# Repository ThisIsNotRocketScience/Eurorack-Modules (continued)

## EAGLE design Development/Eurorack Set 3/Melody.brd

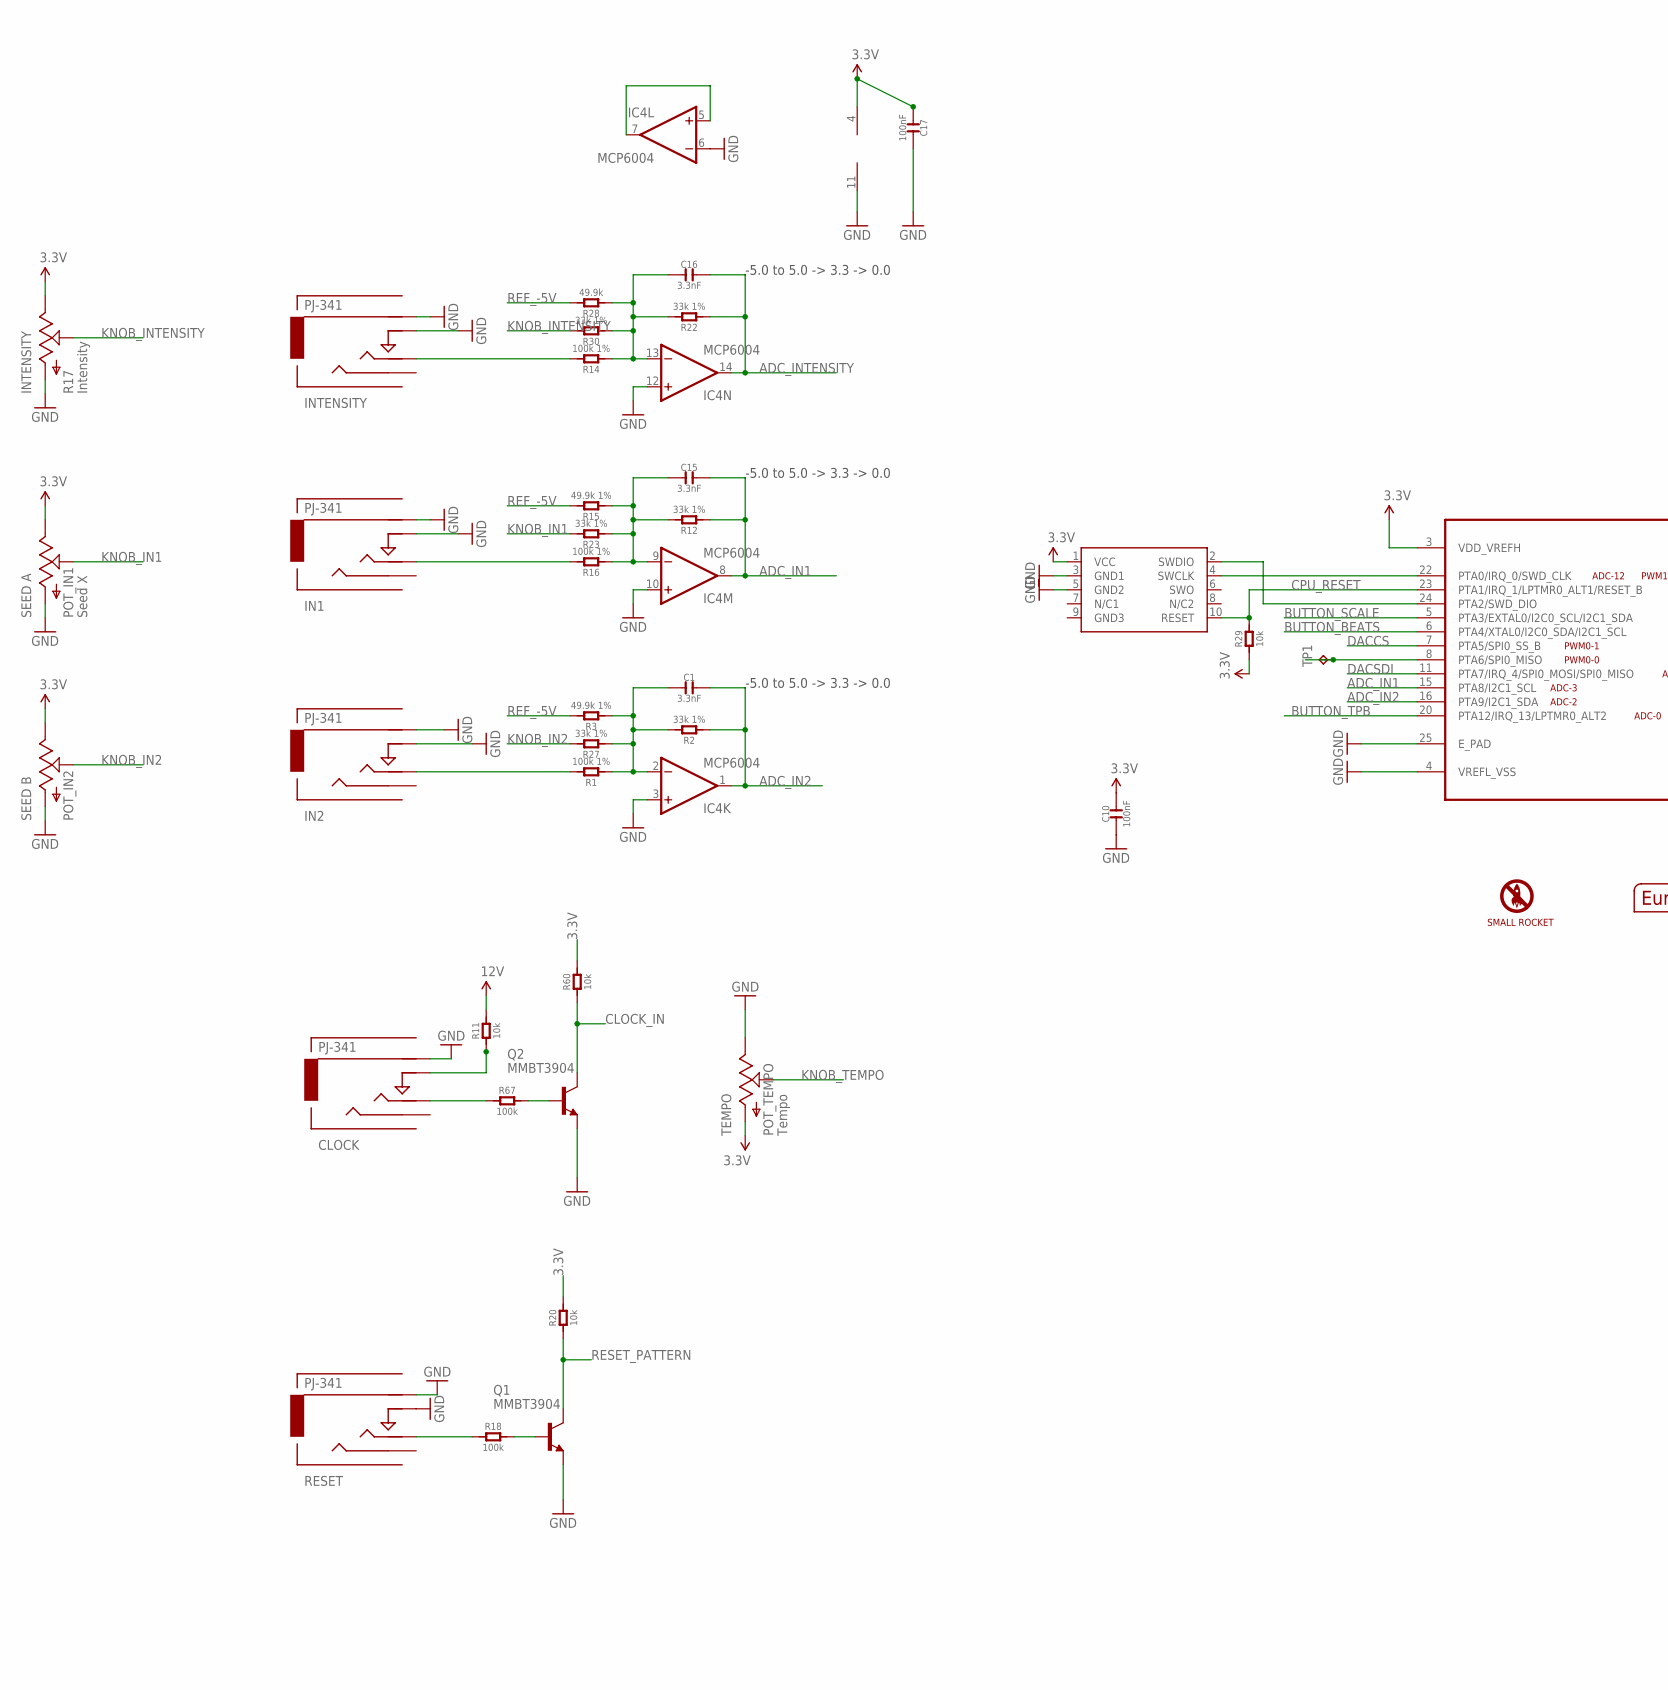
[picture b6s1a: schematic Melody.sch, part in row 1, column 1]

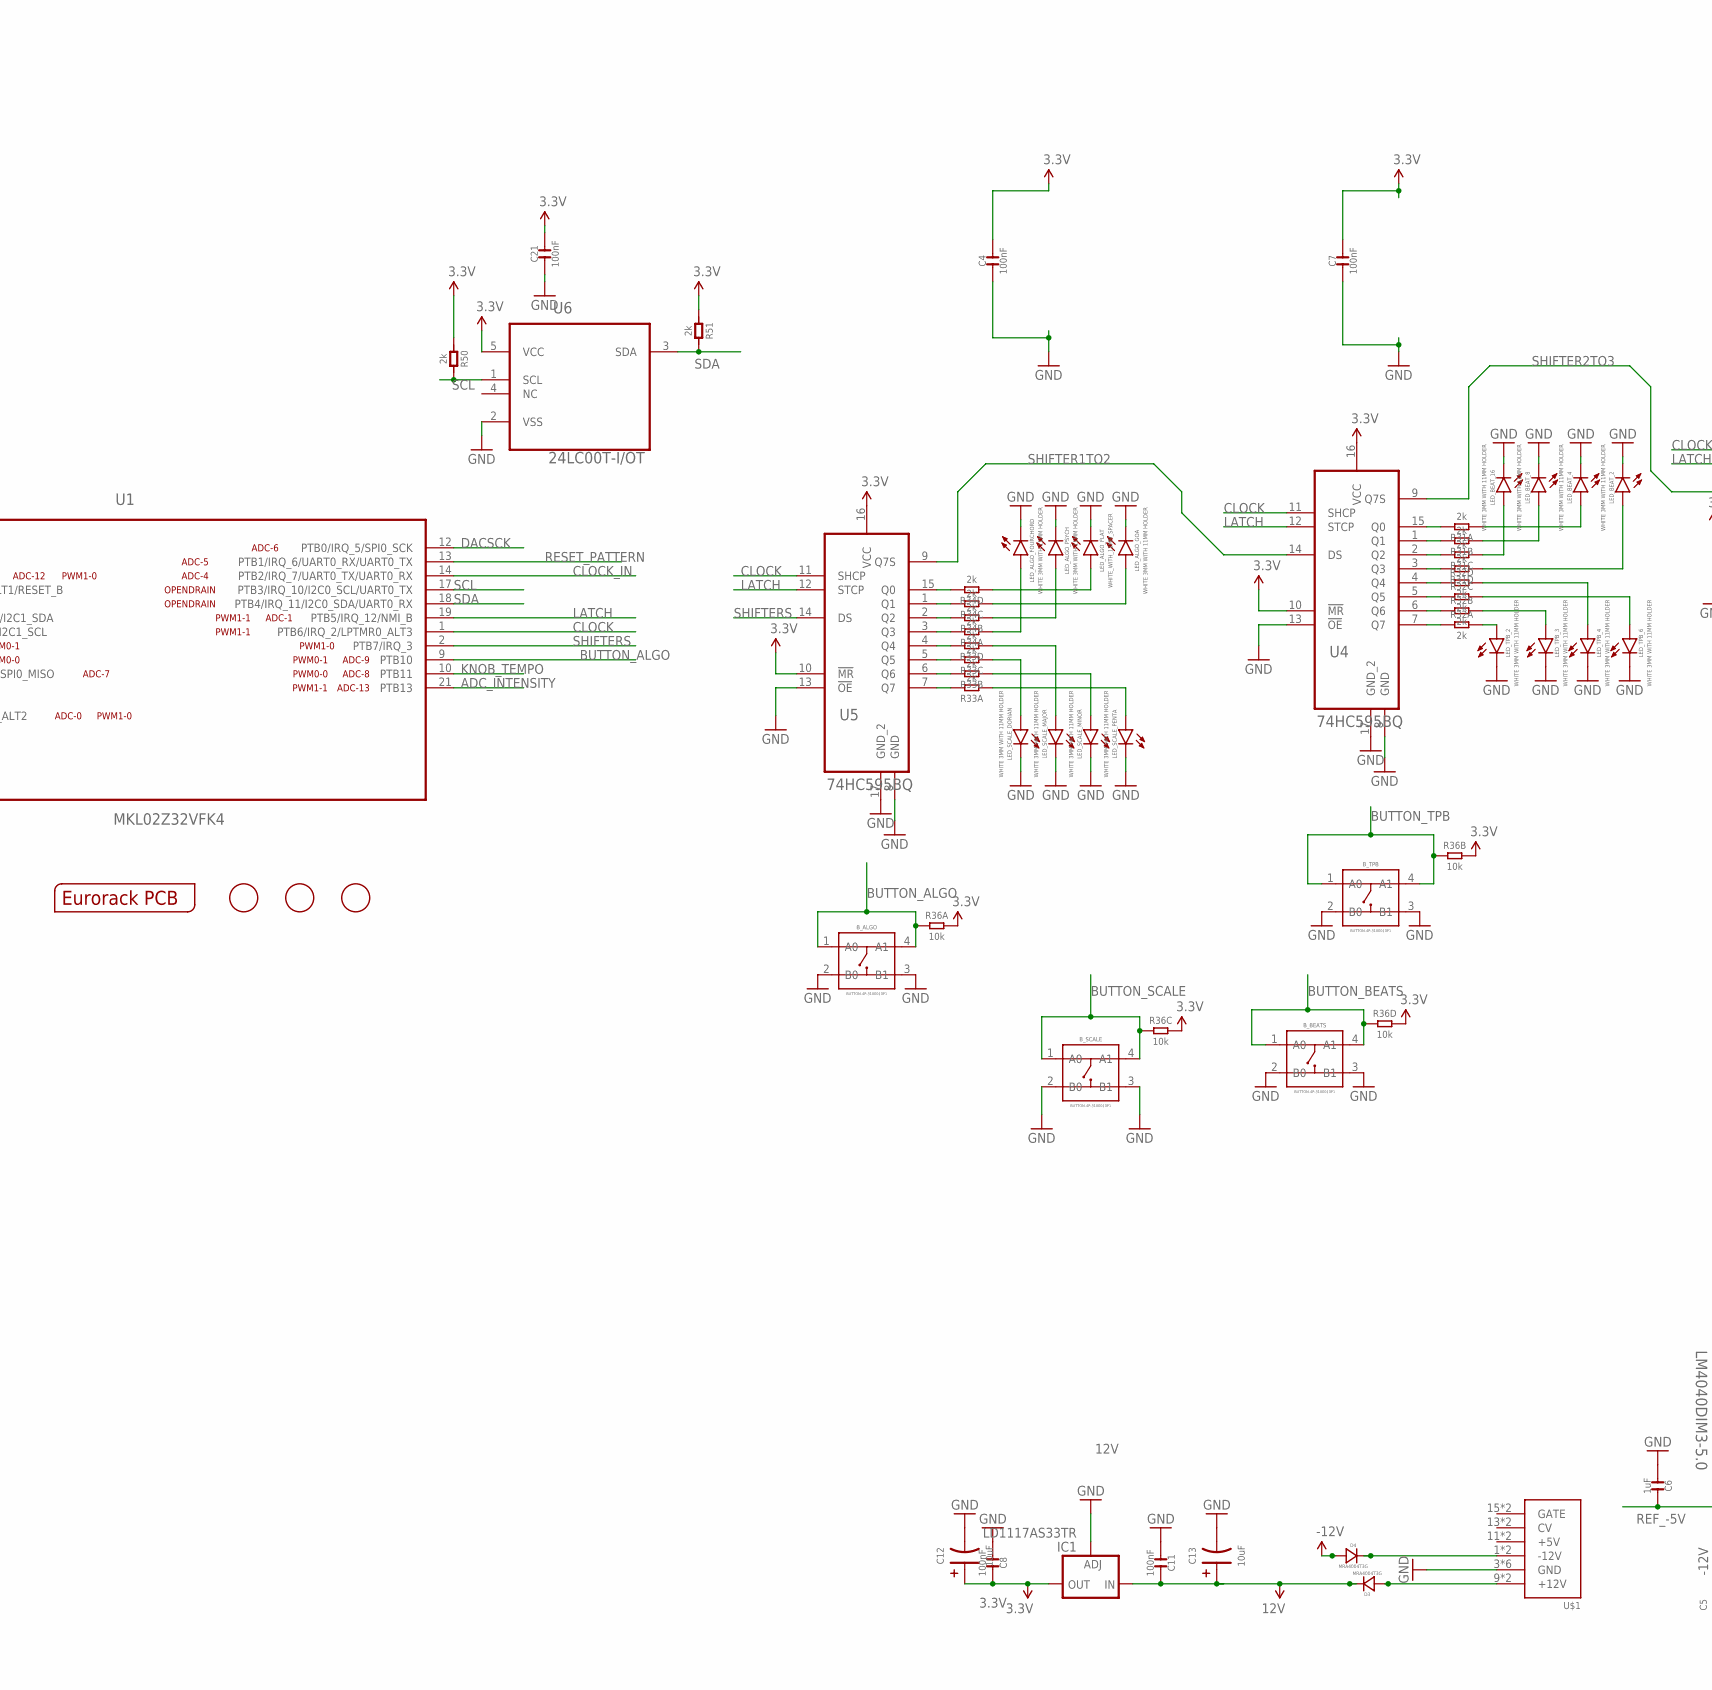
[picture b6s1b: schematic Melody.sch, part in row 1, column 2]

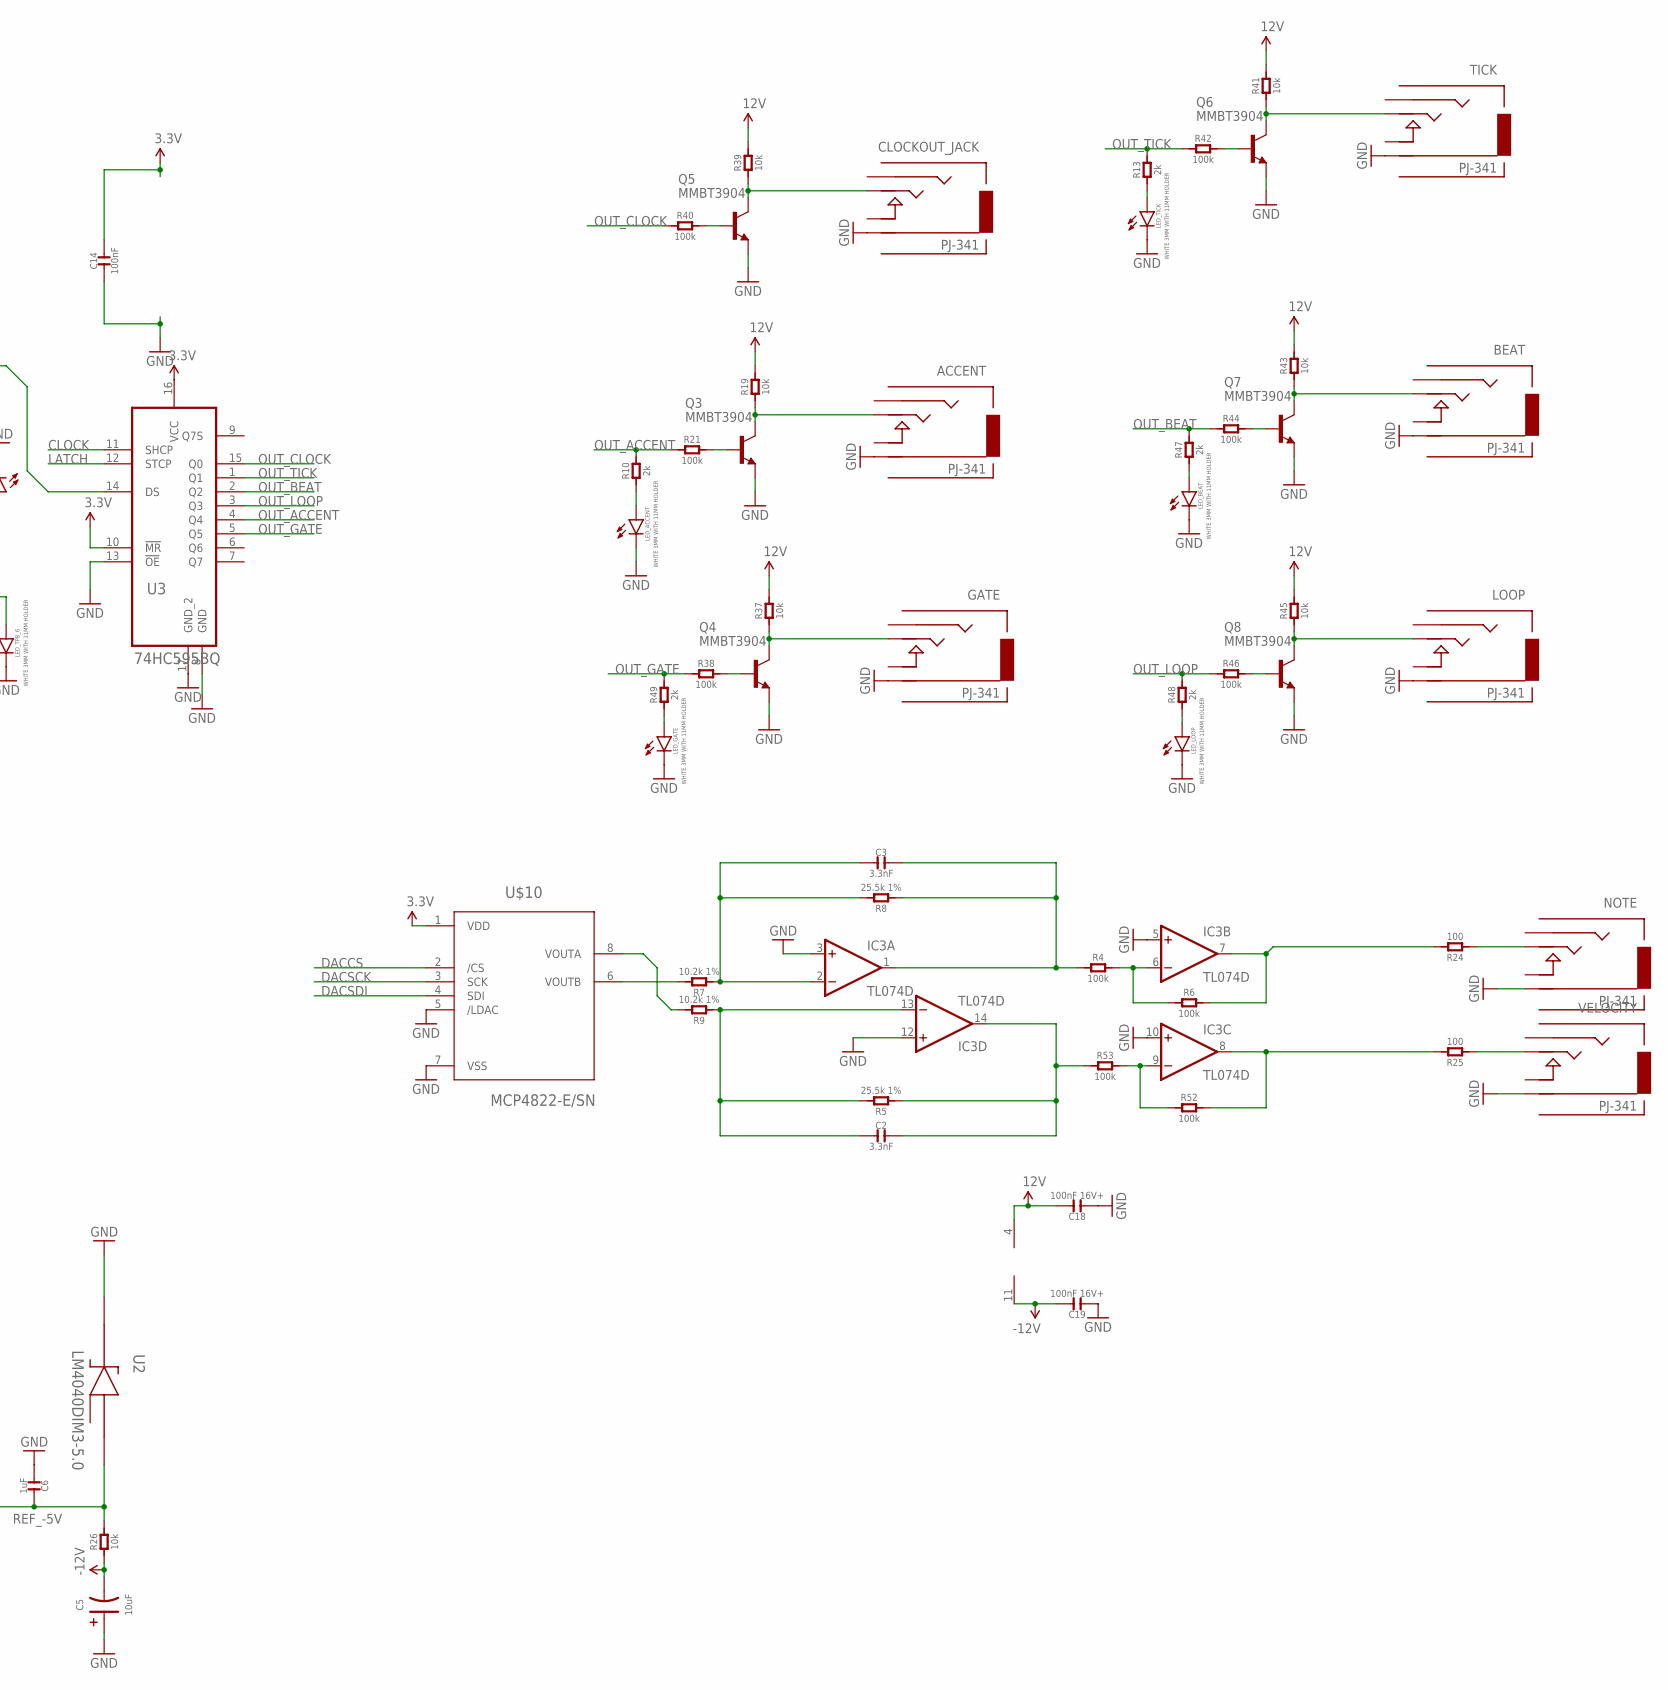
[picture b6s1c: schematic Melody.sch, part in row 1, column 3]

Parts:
ACCENT: PJ-341; 3.5MM-JACK-SWITCH-13MM-OUTPUT
BEAT: PJ-341; 3.5MM-JACK-SWITCH-13MM-OUTPUT
B_ALGO: BUTTON-4P-3100010P1; 4P-SMD-6.0X6.0X5.0H
B_BEATS: BUTTON-4P-3100010P1; 4P-SMD-6.0X6.0X5.0H
B_SCALE: BUTTON-4P-3100010P1; 4P-SMD-6.0X6.0X5.0H
B_TPB: BUTTON-4P-3100010P1; 4P-SMD-6.0X6.0X5.0H
C1, C2, C3, C15, C16: 3.3nF; C0603
C4, C7, C8, C10, C11, C14, C17, C21: 100nF; C0603; MPN MC0603F104Z160CT
C5, C12, C13: 10uF; AVX-A; MPN TAJB106K020RNJ
C6: 1uF; C0603; MPN 06035C104KAT2A
C18, C19: 100nF 16V+; C0603; MPN MC0603F104Z160CT
CLOCK: PJ-341; 3.5MM-JACK-SWITCH-13MM-INPUT
CLOCKOUT_JACK: PJ-341; 3.5MM-JACK-SWITCH-13MM-OUTPUT
D3, D4: MRA4004T3G; DO-214AC; MPN US1G-E3/5AT
GATE: PJ-341; 3.5MM-JACK-SWITCH-13MM-OUTPUT
IC1: LD1117AS33TR; SOT223; MPN LD1117AS33TR
IC3: TL074D; SO14; MPN TL074CD
IC4: MCP6004; SO14; MPN MCP6004-I/SL.
IN1, IN2: PJ-341; 3.5MM-JACK-SWITCH-13MM-INPUT
INTENSITY: PJ-341; 3.5MM-JACK-SWITCH-13MM-INPUT
LED_ACCENT: WHITE 3MM WITH 11MM HOLDER; LED3MM
LED_ALGO_FLAT: WHITE_WITH_11MM_SPACER; LED3MM
LED_ALGO_FOURCHORD: WHITE 3MM WITH 11MM HOLDER; LED3MM
LED_ALGO_GOA: WHITE 3MM WITH 11MM HOLDER; LED3MM
LED_ALGO_PSYCH: WHITE 3MM WITH 11MM HOLDER; LED3MM
LED_BEAT: WHITE 3MM WITH 11MM HOLDER; LED3MM
LED_BEAT_2, LED_BEAT_4, LED_BEAT_8, LED_BEAT_16: WHITE 3MM WITH 11MM HOLDER; LED3MM
LED_GATE: WHITE 3MM WITH 11MM HOLDER; LED3MM
LED_LOOP: WHITE 3MM WITH 11MM HOLDER; LED3MM
LED_SCALE_DORIAN: WHITE 3MM WITH 11MM HOLDER; LED3MM
LED_SCALE_MAJOR: WHITE 3MM WITH 11MM HOLDER; LED3MM
LED_SCALE_MINOR: WHITE 3MM WITH 11MM HOLDER; LED3MM
LED_SCALE_PENTA: WHITE 3MM WITH 11MM HOLDER; LED3MM
LED_TICK: WHITE 3MM WITH 11MM HOLDER; LED3MM
LED_TPB_2, LED_TPB_3, LED_TPB_4, LED_TPB_6: WHITE 3MM WITH 11MM HOLDER; LED3MM
LOOP: PJ-341; 3.5MM-JACK-SWITCH-13MM-OUTPUT
NOTE: PJ-341; 3.5MM-JACK-SWITCH-13MM-OUTPUT
POT_IN1: SEED A; OG-POTS_ALPS_POT_VERTICAL
POT_IN2: SEED B; OG-POTS_ALPS_POT_VERTICAL
POT_TEMPO: TEMPO; OG-POTS_ALPS_POT_VERTICAL
Q1, Q2, Q3, Q4, Q5, Q6, Q7, Q8: MMBT3904; SOT23-BEC; MPN PMBT3904,215
R1, R14, R16: 100k 1%; R0603
R2, R12, R22, R23, R27, R30: 33k 1%; R0603
R3, R15: 49.9k 1%; R0603
R4, R6, R18, R21, R38, R40, R42, R44, R46, R52, R53, R67: 100k; R0603
R5, R8: 25.5k 1%; R0603
R7, R9: 10.2k 1%; R0603
R10, R13, R47, R48, R49, R50, R51: 2k; R0603
R11, R19, R20, R26, R29, R37, R39, R41, R43, R45, R60: 10k; R0603
R17: INTENSITY; OG-POTS_ALPS_POT_VERTICAL
R24, R25: 100; R0603
R28: 49.9k; R0603
R31, R32, R33, R34: 2k; R1206-8
R36: 10k; R1206-8
RESET: PJ-341; 3.5MM-JACK-SWITCH-13MM-INPUT
SWD1: CORTEX_SWD; M50-3600542
TICK: PJ-341; 3.5MM-JACK-SWITCH-13MM-OUTPUT
TP1: TPB1,27; B1,27
U1: MKL02Z32VFK4; QFN50P400X400X100-25N
U2: LM4040DIM3-5.0; SOT95P237X112-3N
U3, U4, U5: 74HC595BQ; QFN50P250X350X100-17N
U6: 24LC00T-I/OT; SOT95P290X145-5N; MPN 24LC00T-I/OT
U$1: POWER; POWER_16
U$2: EURORACK_PCB12HP; EURORACK12HPPCB
U$4, U$7, U$8: FIDUCIAL; FIDUCIAL_1MM
U$10: MCP4822-E/SN; SOIC8-N_MC
U$19: SMALLROCKET
VELOCITY: PJ-341; 3.5MM-JACK-SWITCH-13MM-OUTPUT

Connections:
3.3V: C4.2, C7.2, C8.2, C10.2, C12.+ (1), C14.2, C17.1, C21.2, IC1.2 (OUT), IC1.4 (OUT), IC4.4 (V+), POT_IN1.P$1 (E), POT_IN2.P$1 (E), POT_TEMPO.P$3 (A), R17.P$1 (E), R20.2, R29.1, R36.5 (2), R36.6 (2), R36.7 (2), R36.8 (2), R50.1, R51.1, R60.2, SWD1.1 (VCC), U1.3 (VDD_VREFH), U3.10 (!MR), U3.16 (VCC), U4.10 (!MR), U4.16 (VCC), U5.10 (!MR), U5.16 (VCC), U6.5 (VCC), U$10.1 (VDD)
12V: C11.2, C13.+ (1), C18.2, D3.2 (-), IC1.3 (IN), IC3.4 (V+), R11.2, R19.2, R37.2, R39.2, R41.2, R43.2, R45.2
-12V: C5.- (2), C19.2, D4.1 (+), IC3.11 (V-), R26.1
ADC_IN1: C15.2, IC4.8 (OUT), R12.1, U1.15 (PTA8/I2C1_SCL)
ADC_IN2: C1.2, IC4.1 (OUT), R2.1, U1.16 (PTA9/I2C1_SDA)
ADC_INTENSITY: C16.2, IC4.14 (OUT), R22.1, U1.21 (PTB13)
BUTTON_ALGO: B_ALGO.1 (A0), B_ALGO.4 (A1), R36.1, U1.9 (PTB10)
BUTTON_BEATS: B_BEATS.1 (A0), B_BEATS.4 (A1), R36.4 (1), U1.6 (PTA4/XTAL0/I2C0_SDA/I2C1_SCL)
BUTTON_SCALE: B_SCALE.1 (A0), B_SCALE.4 (A1), R36.3 (1), U1.5 (PTA3/EXTAL0/I2C0_SCL/I2C1_SDA)
BUTTON_TPB: B_TPB.1 (A0), B_TPB.4 (A1), R36.2 (1), U1.20 (PTA12/IRQ_13/LPTMR0_ALT2)
CLOCK: U1.1 (PTB6/IRQ_2/LPTMR0_ALT3), U3.11 (SHCP), U4.11 (SHCP), U5.11 (SHCP)
CLOCK_IN: Q2.C, R60.1, U1.14 (PTB2/IRQ_7/UART0_TX/UART0_RX)
CPU_RESET: R29.2, SWD1.10 (RESET), U1.23 (PTA1/IRQ_1/LPTMR0_ALT1/RESET_B)
DACCS: U1.7 (PTA5/SPI0_SS_B), U$10.2 (/CS)
DACSCK: U1.12 (PTB0/IRQ_5/SPI0_SCK), U$10.3 (SCK)
DACSDI: U1.11 (PTA7/IRQ_4/SPI0_MOSI/SPI0_MISO), U$10.4 (SDI)
GND: ACCENT.RING@3 (RING), BEAT.RING@3 (RING), B_ALGO.2 (B0), B_ALGO.3 (B1), B_BEATS.2 (B0), B_BEATS.3 (B1), B_SCALE.2 (B0), B_SCALE.3 (B1), B_TPB.2 (B0), B_TPB.3 (B1), C4.1, C5.+ (1), C6.1, C7.1, C8.1, C10.1, C11.1, C12.- (2), C13.- (2), C14.1, C17.2, C18.1, C19.1, C21.1, CLOCK.RING@3 (RING), CLOCKOUT_JACK.RING@3 (RING), GATE.RING@3 (RING), IC1.1 (ADJ), IC3.3 (+IN), IC3.5 (+IN), IC3.10 (+IN), IC3.12 (+IN), IC4.3 (+IN), IC4.6 (-IN), IC4.10 (+IN), IC4.11 (V-), IC4.12 (+IN), IN1.RING@3 (RING), IN1.SWITCH@3 (SWITCH), IN2.RING@3 (RING), IN2.SWITCH@3 (SWITCH), INTENSITY.RING@3 (RING), INTENSITY.SWITCH@3 (SWITCH), LED_ACCENT.K (C), LED_ALGO_FLAT.K (C), LED_ALGO_FOURCHORD.K (C), LED_ALGO_GOA.K (C), LED_ALGO_PSYCH.K (C), LED_BEAT.K (C), LED_BEAT_2.K (C), LED_BEAT_4.K (C), LED_BEAT_8.K (C), LED_BEAT_16.K (C), LED_GATE.K (C), LED_LOOP.K (C), LED_SCALE_DORIAN.K (C), LED_SCALE_MAJOR.K (C), LED_SCALE_MINOR.K (C), LED_SCALE_PENTA.K (C), LED_TICK.K (C), LED_TPB_2.K (C), LED_TPB_3.K (C), LED_TPB_4.K (C), LED_TPB_6.K (C), LOOP.RING@3 (RING), NOTE.RING@3 (RING), POT_IN1.P$3 (A), POT_IN2.P$3 (A), POT_TEMPO.P$1 (E), Q1.E, Q2.E, Q3.E, Q4.E, Q5.E, Q6.E, Q7.E, Q8.E, R17.P$3 (A), RESET.RING@3 (RING), RESET.SWITCH@3 (SWITCH), SWD1.3 (GND1), SWD1.5 (GND2), TICK.RING@3 (RING), U1.4 (VREFL_VSS), U1.25 (E_PAD), U2.1 (CATHODE), U3.8 (GND), U3.13 (!OE), U3.17 (GND_2), U4.8 (GND), U4.13 (!OE), U4.17 (GND_2), U5.8 (GND), U5.13 (!OE), U5.17 (GND_2), U6.2 (VSS), U$1.3 (GND), U$1.4 (GND), U$1.5 (GND), U$1.6 (GND), U$1.7 (GND), U$1.8 (GND), U$10.5 (/LDAC), U$10.7 (VSS), VELOCITY.RING@3 (RING)
KNOB_IN1: POT_IN1.P$2 (S), R23.2
KNOB_IN2: POT_IN2.P$2 (S), R27.2
KNOB_INTENSITY: R17.P$2 (S), R30.2
KNOB_TEMPO: POT_TEMPO.P$2 (S), U1.10 (PTB11)
LATCH: U1.19 (PTB5/IRQ_12/NMI_B), U3.12 (STCP), U4.12 (STCP), U5.12 (STCP)
unnamed: R31.7 (2), U4.1 (Q1)
unnamed: IC3.6 (-IN), R4.2, R6.1
unnamed: IN1.TIP@3 (TIP), R16.2
unnamed: C15.1, IC4.9 (-IN), R12.2, R15.1, R16.1, R23.1
unnamed: R9.2, U$10.8 (VOUTA)
unnamed: IN2.TIP@3 (TIP), R1.2
unnamed: R7.2, U$10.6 (VOUTB)
unnamed: C1.1, IC4.2 (-IN), R1.1, R2.2, R3.1, R27.1
unnamed: C2.1, IC3.13 (-IN), R5.2, R9.1
unnamed: C3.1, IC3.2 (-IN), R7.1, R8.2
unnamed: D3.1 (+), U$1.9 (+12V), U$1.10 (+12V)
unnamed: IC3.7 (OUT), R6.2, R24.2
unnamed: Q1.B, R18.2
unnamed: R18.1, RESET.TIP@3 (TIP)
unnamed: IC3.9 (-IN), R52.1, R53.2
unnamed: C3.2, IC3.1 (OUT), R4.1, R8.1
unnamed: R31.6 (2), U4.2 (Q2)
unnamed: R25.1, VELOCITY.TIP@3 (TIP)
unnamed: NOTE.TIP@3 (TIP), R24.1
unnamed: C2.2, IC3.14 (OUT), R5.1, R53.1
unnamed: Q3.B, R21.2
unnamed: R31.5 (2), U4.3 (Q3)
unnamed: R32.4 (1), U4.4 (Q4)
unnamed: LED_SCALE_DORIAN.A, R33.6 (2)
unnamed: ACCENT.TIP@3 (TIP), Q3.C, R19.1
unnamed: R32.3 (1), U4.5 (Q5)
unnamed: R32.2 (1), U4.6 (Q6)
unnamed: LED_SCALE_MAJOR.A, R33.5 (2)
unnamed: INTENSITY.TIP@3 (TIP), R14.2
unnamed: C16.1, IC4.13 (-IN), R14.1, R22.2, R28.1, R30.1
unnamed: R32.1, U4.7 (Q7)
unnamed: R31.8 (2), U4.15 (Q0)
unnamed: R34.4 (1), U5.15 (Q0)
unnamed: R34.3 (1), U5.1 (Q1)
unnamed: R34.2 (1), U5.2 (Q2)
unnamed: R34.1, U5.3 (Q3)
unnamed: R33.4 (1), U5.4 (Q4)
unnamed: R33.3 (1), U5.5 (Q5)
unnamed: CLOCK.TIP@3 (TIP), R67.1
unnamed: R33.2 (1), U5.6 (Q6)
unnamed: R33.1, U5.7 (Q7)
unnamed: Q4.B, R38.2
unnamed: GATE.TIP@3 (TIP), Q4.C, R37.1
unnamed: Q5.B, R40.2
unnamed: CLOCKOUT_JACK.TIP@3 (TIP), Q5.C, R39.1
unnamed: Q6.B, R42.2
unnamed: D4.2 (-), U$1.1 (-12V), U$1.2 (-12V)
unnamed: Q6.C, R41.1, TICK.TIP@3 (TIP)
unnamed: Q2.B, R67.2
unnamed: Q7.B, R44.2
unnamed: BEAT.TIP@3 (TIP), Q7.C, R43.1
unnamed: Q8.B, R46.2
unnamed: LOOP.TIP@3 (TIP), Q8.C, R45.1
unnamed: LED_ALGO_GOA.A, R34.6 (2)
unnamed: LED_ALGO_FLAT.A, R34.5 (2)
unnamed: LED_ALGO_PSYCH.A, R34.7 (2)
unnamed: LED_ALGO_FOURCHORD.A, R34.8 (2)
unnamed: LED_SCALE_MINOR.A, R33.7 (2)
unnamed: LED_SCALE_PENTA.A, R33.8 (2)
unnamed: LED_BEAT_16.A, R31.3 (1)
unnamed: LED_BEAT_8.A, R31.2 (1)
unnamed: LED_BEAT_4.A, R31.1
unnamed: LED_BEAT_2.A, R31.4 (1)
unnamed: LED_TPB_2.A, R32.8 (2)
unnamed: LED_TPB_3.A, R32.7 (2)
unnamed: LED_TPB_4.A, R32.5 (2)
unnamed: LED_TPB_6.A, R32.6 (2)
unnamed: LED_TICK.A, R13.1
unnamed: LED_LOOP.A, R48.1
unnamed: LED_GATE.A, R49.1
unnamed: LED_BEAT.A, R47.1
unnamed: IC3.8 (OUT), R25.2, R52.2
unnamed: LED_ACCENT.A, R10.1
unnamed: CLOCK.SWITCH@3 (SWITCH), R11.1
unnamed: IC4.5 (+IN), IC4.7 (OUT)
OUT_ACCENT: R10.2, R21.1, U3.4 (Q4)
OUT_BEAT: R44.1, R47.2, U3.2 (Q2)
OUT_CLOCK: R40.1, U3.15 (Q0)
OUT_GATE: R38.1, R49.2, U3.5 (Q5)
OUT_LOOP: R46.1, R48.2, U3.3 (Q3)
OUT_TICK: R13.2, R42.1, U3.1 (Q1)
PTA6: TP1.TP, U1.8 (PTA6/SPI0_MISO)
REF_-5V: C6.2, R3.2, R15.2, R26.2, R28.2, U2.2 (ANODE)
RESET_PATTERN: Q1.C, R20.1, U1.13 (PTB1/IRQ_6/UART0_RX/UART0_TX)
SCL: R50.2, U1.17 (PTB3/IRQ_10/I2C0_SCL/UART0_TX), U6.1 (SCL)
SDA: R51.2, U1.18 (PTB4/IRQ_11/I2C0_SDA/UART0_RX), U6.3 (SDA)
SHIFTER1TO2: U4.14 (DS), U5.9 (Q7S)
SHIFTER2TO3: U3.14 (DS), U4.9 (Q7S)
SHIFTERS: U1.2 (PTB7/IRQ_3), U5.14 (DS)
SWD_CLK: SWD1.4 (SWCLK), U1.22 (PTA0/IRQ_0/SWD_CLK)
SWD_DIO: SWD1.2 (SWDIO), U1.24 (PTA2/SWD_DIO)

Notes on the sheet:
-5.0 to 5.0 -> 3.3 -> 0.0

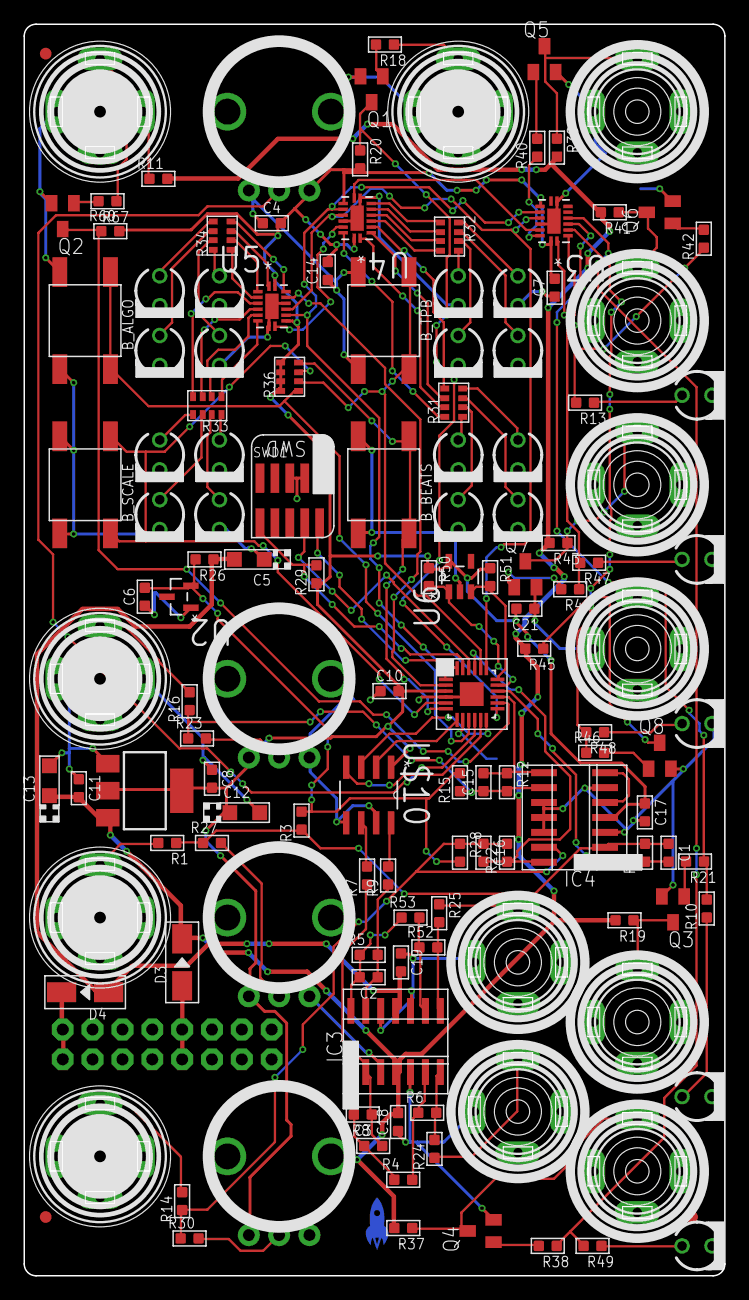
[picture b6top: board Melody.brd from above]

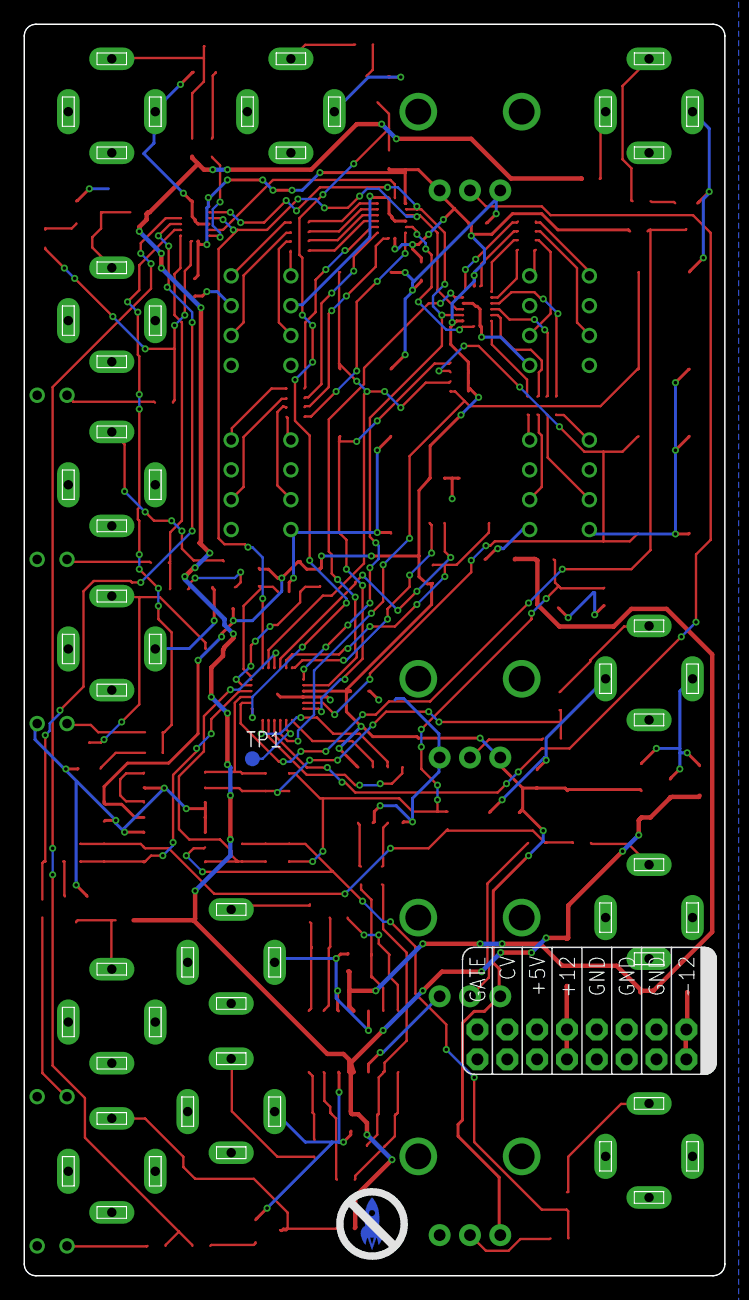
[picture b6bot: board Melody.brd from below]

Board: 2 copper layers, 59.6 x 106.5 mm, 142 parts (3 on the bottom side), 113 nets.

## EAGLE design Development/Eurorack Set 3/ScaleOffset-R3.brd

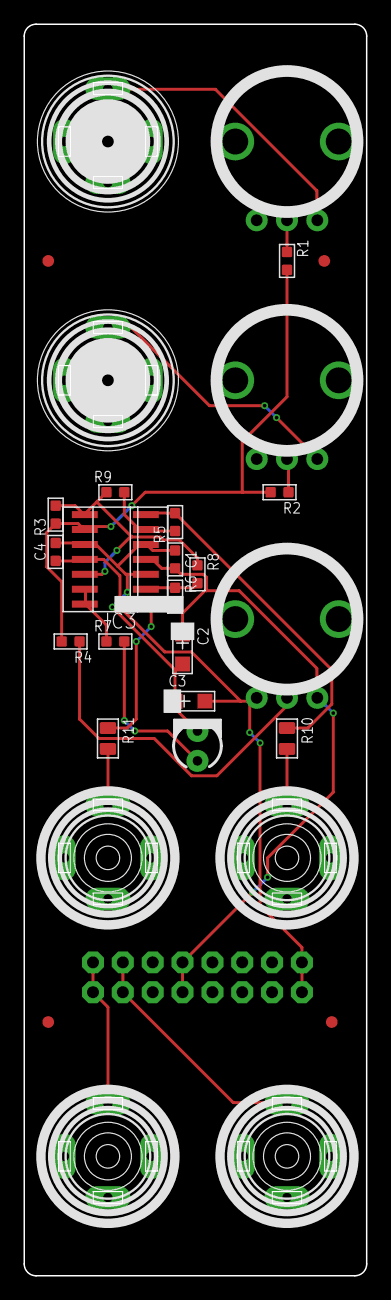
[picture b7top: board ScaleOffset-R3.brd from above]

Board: 2 copper layers, 29.1 x 106.5 mm, 32 parts (1 on the bottom side), 20 nets.

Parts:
C1, C4: 100n; C0603
C2, C3: AVX-A
CV: CV; 3.5MM-JACK-SWITCH-13MM-OUTPUT
GAIN1: Gain 1; OG-POTS_ALPS_POT_VERTICAL
GAIN2: Gain 2; OG-POTS_ALPS_POT_VERTICAL
GATE: GATE; 3.5MM-JACK-SWITCH-13MM-OUTPUT
IC3: TL074D; SO14
IN1: Input 1; 3.5MM-JACK-SWITCH-13MM-INPUT
IN2: Input 2; 3.5MM-JACK-SWITCH-13MM-INPUT
LED1: REDBLUE; LED3MM
OFFSET: Offset; OG-POTS_ALPS_POT_VERTICAL
OUT1: 2; 3.5MM-JACK-SWITCH-13MM-OUTPUT
OUT2: 1; 3.5MM-JACK-SWITCH-13MM-OUTPUT
R1, R2, R3, R4, R8, R9: 100k; R0603
R5, R6: 100K; R0603
R7: 1k; R0603
R10, R11: 51; C0805
U$1, U$2, U$3, U$4: FIDUCIAL; FIDUCIAL_1MM
U$5: POWER; POWER_16
U$12: EURORACK_PCB6HP; EURORACK6HPPCB

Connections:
12V: C1.2, C2.+, IC3.4, OFFSET.P$3, U$5.9, U$5.10
-12V: C3.-, C4.1, IC3.11, OFFSET.P$1, U$5.1, U$5.2
CV: CV.TIP@3, U$5.13, U$5.14
FBOUT1: IC3.7, R5.2, R10.1
FBOUT2: IC3.1, R6.2, R11.1
GATE: GATE.TIP@3, U$5.15, U$5.16
GND: C1.1, C2.-, C3.+, C4.2, CV.RING@3, GAIN1.P$1, GAIN2.P$1, GATE.RING@3, IC3.3, IC3.5, IC3.10, IN1.RING@3, IN1.SWITCH@3, IN2.RING@3, IN2.SWITCH@3, LED1.K, OUT1.RING@3, OUT2.RING@3, U$5.3, U$5.4, U$5.5, U$5.6, U$5.7, U$5.8
unnamed: IC3.6, R5.1, R9.2
unnamed: LED1.A, R7.2
unnamed: GAIN2.P$3, IN2.TIP@3
unnamed: GAIN1.P$3, IN1.TIP@3
unnamed: GAIN1.P$2, R1.1
unnamed: GAIN2.P$2, R2.1
unnamed: IC3.8, IC3.12, R3.2, R8.1, R9.1
unnamed: IC3.13, IC3.14, R7.1
unnamed: IC3.2, R6.1, R8.2
OFFSET: OFFSET.P$2, R4.1
OUT1: OUT1.TIP@3, R10.2
OUT2: OUT2.TIP@3, R11.2
SUMMING: IC3.9, R1.2, R2.2, R3.1, R4.2
